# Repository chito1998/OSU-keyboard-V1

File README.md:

# OSU-keyboard-V1
 My very first keyboard. Hopefully everything goes well :'v

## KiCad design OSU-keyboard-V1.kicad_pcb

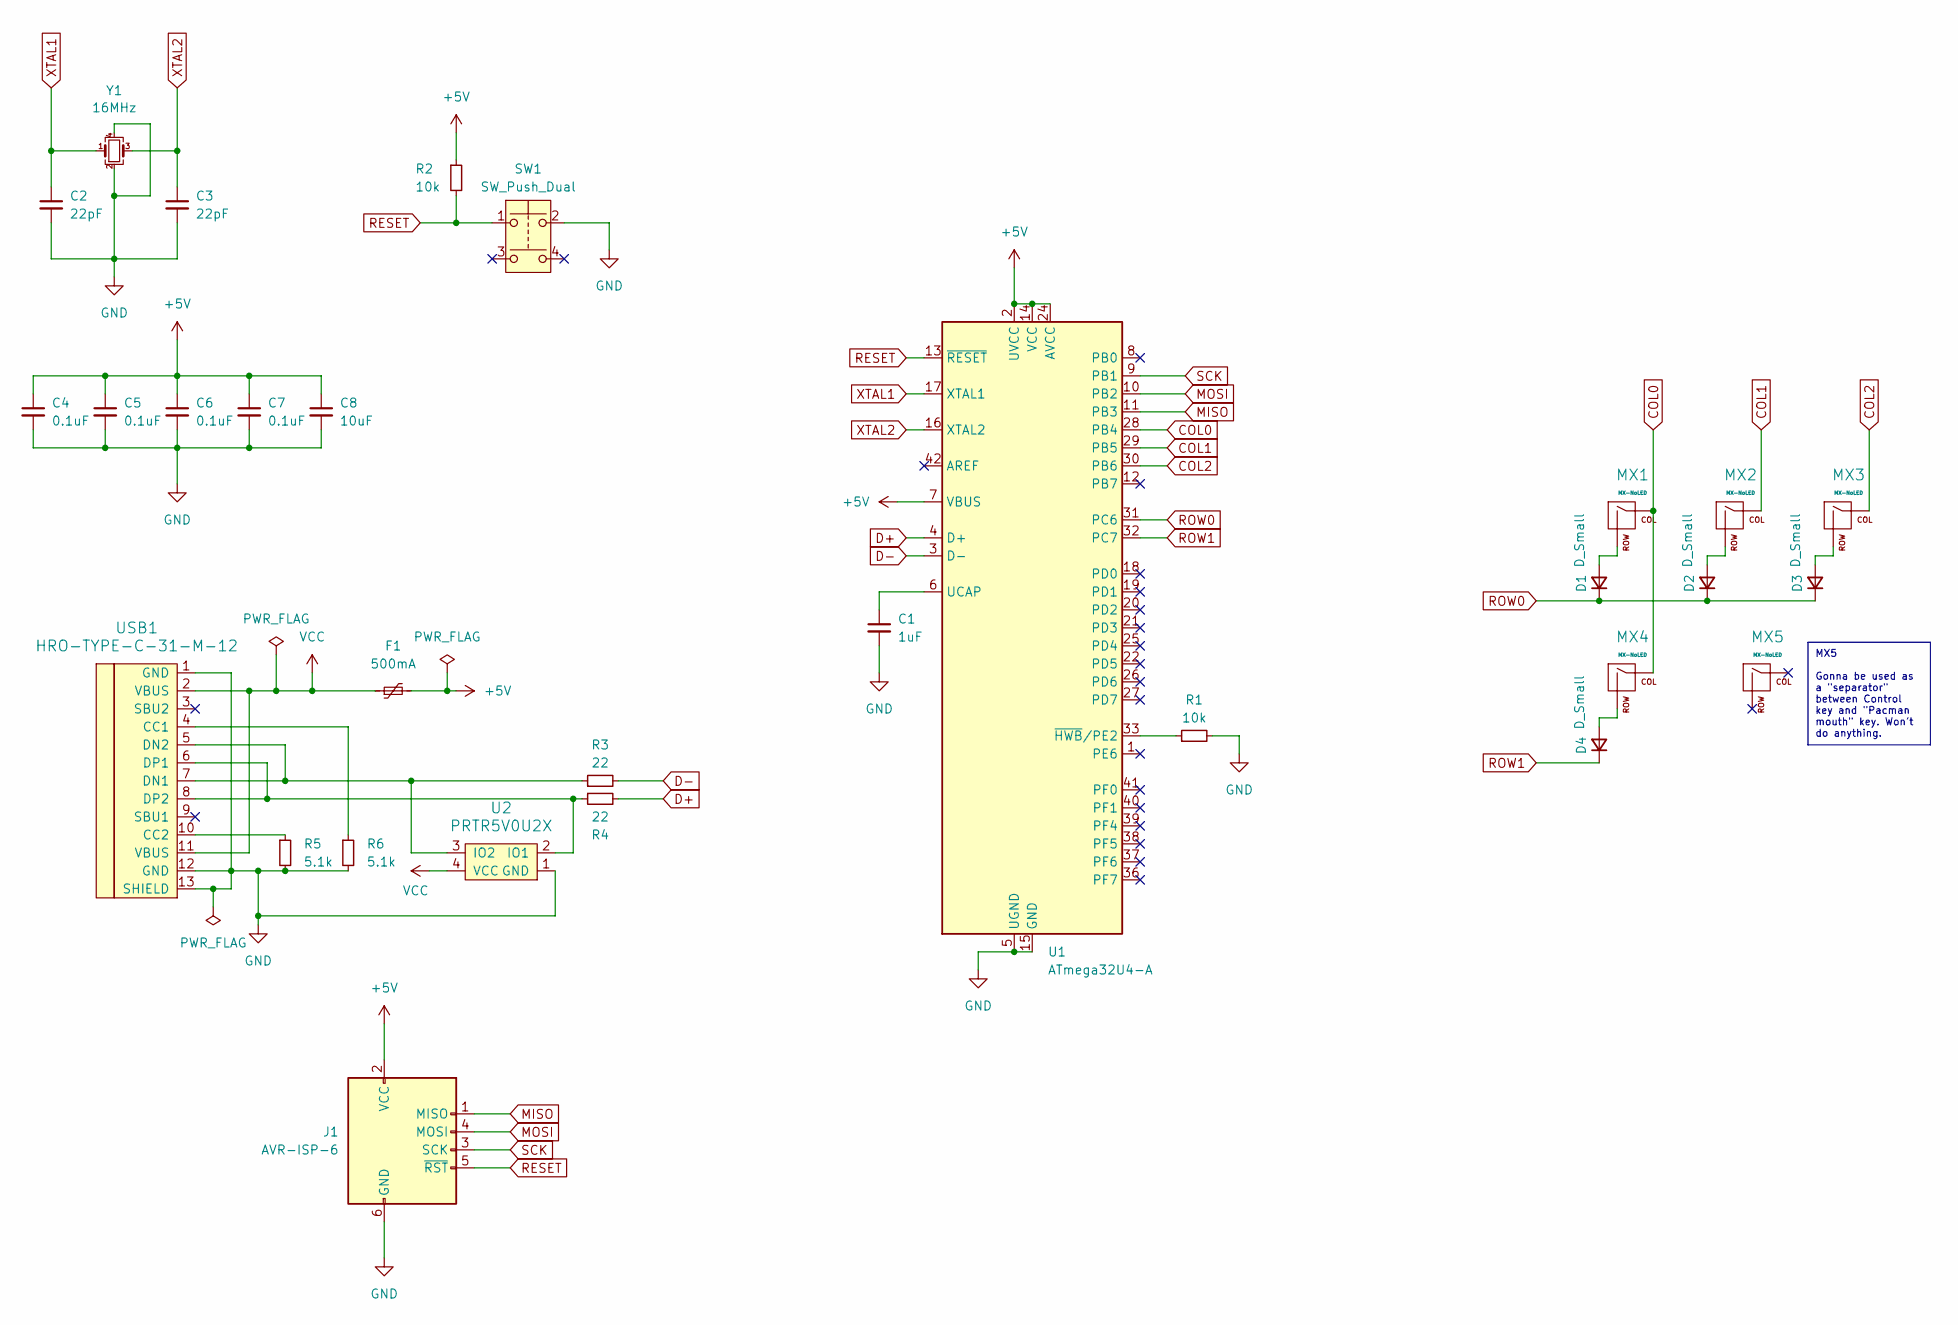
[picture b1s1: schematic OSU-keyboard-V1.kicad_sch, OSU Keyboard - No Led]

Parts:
C1: 1uF; C_0805_2012Metric_Pad1.18x1.45mm_HandSolder
C2, C3: 22pF; C_0805_2012Metric_Pad1.18x1.45mm_HandSolder
C4, C5, C6, C7: 0.1uF; C_0805_2012Metric_Pad1.18x1.45mm_HandSolder
C8: 10uF; C_0805_2012Metric_Pad1.18x1.45mm_HandSolder
D1, D2, D3, D4: D_Small; D_SOD-123
F1: 500mA; Fuse_1206_3216Metric_Pad1.42x1.75mm_HandSolder
J1: AVR-ISP-6; Reset_Pretty-Mask
MX1, MX2, MX3: MX-NoLED; MX-1U
MX4: MX-NoLED; MX-1.5U
MX5: MX-NoLED; MX-1.25U
R1, R2: 10k; R_0805_2012Metric_Pad1.20x1.40mm_HandSolder
R3, R4: 22; R_0805_2012Metric_Pad1.20x1.40mm_HandSolder
R5, R6: 5.1k; R_0805_2012Metric_Pad1.20x1.40mm_HandSolder
SW1: SW_Push_Dual; SW_SPST_SKQG_WithStem
U1: ATmega32U4-A; TQFP-44_10x10mm_P0.8mm
U2: PRTR5V0U2X; SOT143B
USB1: HRO-TYPE-C-31-M-12; HRO-TYPE-C-31-M-12-HandSoldering
Y1: 16MHz; Crystal_SMD_3225-4Pin_3.2x2.5mm_HandSoldering

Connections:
+5V: C4.1, C5.1, C6.1, C7.1, C8.1, F1.2, J1.2 (VCC), R2.1, U1.2 (UVCC), U1.7 (VBUS), U1.14 (VCC), U1.24 (AVCC), U1.34 (VCC), U1.44 (AVCC)
COL0: MX1.1 (COL), MX4.1 (COL), U1.28 (PB4)
COL1: MX2.1 (COL), U1.29 (PB5)
COL2: MX3.1 (COL), U1.30 (PB6)
D+: R4.2, U1.4 (D+)
D-: R3.2, U1.3 (D-)
GND: C1.2, C2.2, C3.2, C4.2, C5.2, C6.2, C7.2, C8.2, J1.6 (GND), R1.2, R5.2, R6.2, SW1.2, U1.5 (UGND), U1.15 (GND), U1.23 (GND), U1.35 (GND), U1.43 (GND), U2.1 (GND), USB1.1 (GND), USB1.12 (GND), USB1.13 (SHIELD), Y1.2, Y1.4
MISO: J1.1 (MISO), U1.11 (PB3)
MOSI: J1.4 (MOSI), U1.10 (PB2)
unnamed: D1.2 (A), MX1.2 (ROW)
unnamed: D2.2 (A), MX2.2 (ROW)
unnamed: D3.2 (A), MX3.2 (ROW)
unnamed: D4.2 (A), MX4.2 (ROW)
unnamed: C1.1, U1.6 (UCAP)
unnamed: R1.1, U1.33 (~HWB/PE2)
unnamed: R4.1, U2.2 (IO1), USB1.6 (DP1), USB1.8 (DP2)
unnamed: R3.1, U2.3 (IO2), USB1.5 (DN2), USB1.7 (DN1)
unnamed: R6.1, USB1.4 (CC1)
unnamed: R5.1, USB1.10 (CC2)
RESET: J1.5 (~RST), R2.2, SW1.1, U1.13 (~RESET)
ROW0: D1.1 (K), D2.1 (K), D3.1 (K), U1.31 (PC6)
ROW1: D4.1 (K), U1.32 (PC7)
SCK: J1.3 (SCK), U1.9 (PB1)
VCC: F1.1, U2.4 (VCC), USB1.2 (VBUS), USB1.11 (VBUS)
XTAL1: C2.1, U1.17 (XTAL1), Y1.1
XTAL2: C3.1, U1.16 (XTAL2), Y1.3

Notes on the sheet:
MX5 Gonna be used as a "separator" between Control key and "Pacman mouth" key. Won't do anything.

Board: 2 copper layers, 30 parts (24 on the bottom side), 26 nets, no tracks yet.

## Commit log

2025-03-22 Setting up project
    Just starting the project :P
2025-03-22 Libraries
    Adding libraries
2025-03-22 Doing extra things for libraries
    I've "isntalled" ebalster’s library.
2025-03-22 Finishing all components
    Just components. For now there is no keyboard components.
2025-03-22 Schematic finish
    Just about to enter to PCB
2025-03-22 Placing components in PCB
    Placing all of them (for the first time)
2025-03-22 Tracing roads
